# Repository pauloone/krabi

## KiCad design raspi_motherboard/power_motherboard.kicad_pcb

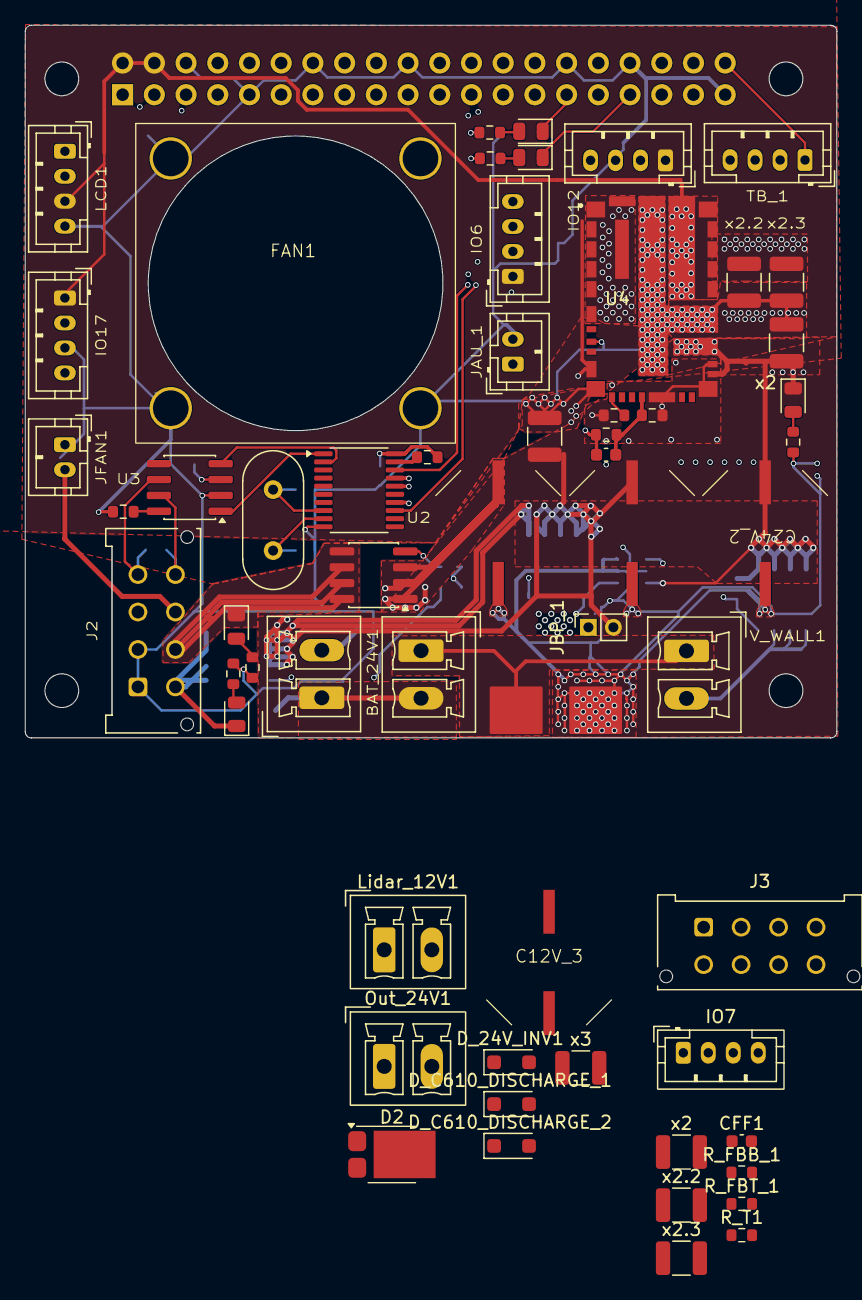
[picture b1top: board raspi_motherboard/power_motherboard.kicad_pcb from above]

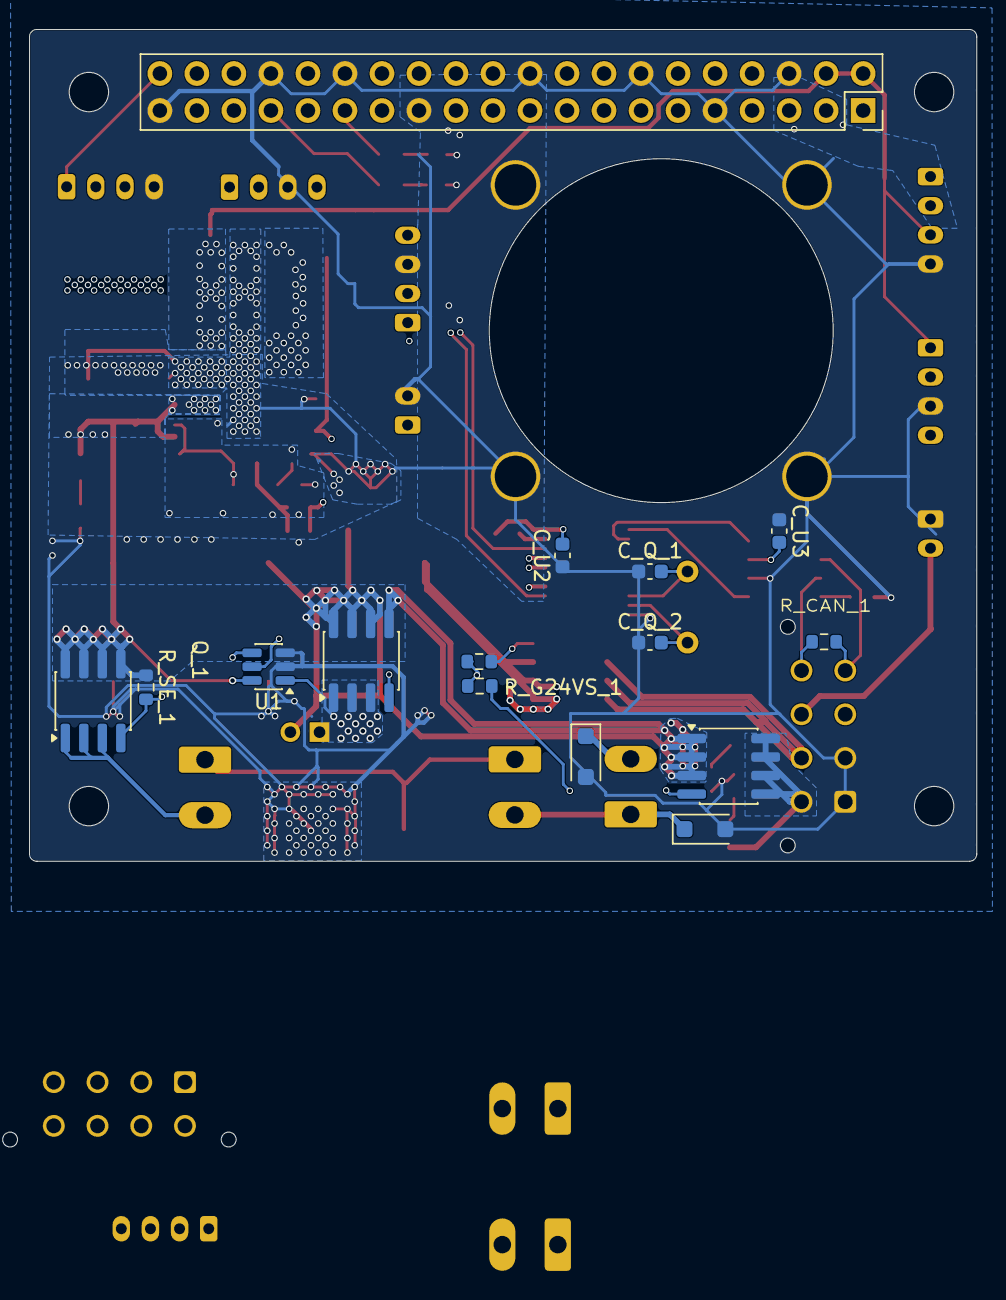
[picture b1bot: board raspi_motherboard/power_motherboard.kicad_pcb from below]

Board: 4 copper layers, 65.0 x 57.1 mm, 78 parts (15 on the bottom side), 48 nets.

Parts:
BAT_12V1, BAT_24V1: Conn_01x02_Pin; PhoenixContact_MCV_1,5_2-G-3.81_1x02_P3.81mm_Vertical
C12V_1, C12V_3, C24V_1, C24V_2: 470µ; CP_Panasonic FN Series G size
C24_V3: 47µ; C_1210_3225Metric
CFF1: C; C_0603_1608Metric
CFF1#2: 58pF; C_0603_1608Metric
C_Q_1, C_Q_2: 22pF; C_0603_1608Metric
C_U2, C_U3: 100nF; C_0603_1608Metric
D2: PMEG045V100EPD; Nexperia_CFP15_SOT-1289
D_12V_INV1, D_24V_INV1, D_24V_INV1#2: D; D_SOD-123F
D_C610_DISCHARGE_1, D_C610_DISCHARGE_2: D; D_SOD-123F
FAN1: Conn_01x02_Socket; FAN_25mm
F_12VE1: Fuse; LittleFuse 154 holder
IO6, IO7, IO12, IO17: Conn_01x04_Socket; JST_PH_B4B-PH-K_1x04_P2.00mm_Vertical
J1: GPIO; PinSocket_2x20_P2.54mm_Vertical
J2, J3: Conn_02x04_Top_Bottom; Molex_Micro-Fit_3.0_43045-0812_2x04_P3.00mm_Vertical
JAU_1: Conn_01x02_Socket; JST_PH_B2B-PH-K_1x02_P2.00mm_Vertical
JBP_1: Conn_01x02_Socket; PinSocket_1x02_P2.00mm_Vertical
JFAN1: Conn_01x02_Socket; JST_PH_B2B-PH-K_1x02_P2.00mm_Vertical
LCD1: Conn_01x04_Socket; JST_PH_B4B-PH-K_1x04_P2.00mm_Vertical
LED_12VS1, LED_24V1, LED_24VS1: LED; LED_0805_2012Metric
LED_R_1, LED_R_2: LED; LED_0805_2012Metric
Lidar_12V1: Conn_01x02_Pin; PhoenixContact_MCV_1,5_2-G-3.81_1x02_P3.81mm_Vertical
MH1, MH2, MH3, MH4: MountingHole_2.7mm_M2.5
Out_24V1: Conn_01x02_Pin; PhoenixContact_MCV_1,5_2-G-3.81_1x02_P3.81mm_Vertical
Q_1, Q_2, Q_12VP_1, Q_24VP_1: RS3L110AT; SOP-8_3.76x4.96mm_P1.27mm
R_CAN_1: 120; R_0603_1608Metric
R_FBB_1, R_FBB_1#2: 10k; R_0603_1608Metric
R_FBT_1, R_FBT_1#2: 41.2k; R_0603_1608Metric
R_G12VS_1, R_G24VS_1: 2.2k; R_0603_1608Metric
R_L12VS1: 2.49k; R_0603_1608Metric
R_L24V1, R_L24VS1: 11k; R_0603_1608Metric
R_LED_R_1, R_LED_R_2: 560; R_0603_1608Metric
R_RESET_1: 10k; R_0603_1608Metric
R_RESET_2: 1k; R_0603_1608Metric
R_SE_1: 470k; R_0603_1608Metric
R_T1, R_T1#2: 25.5k; R_0603_1608Metric
TB_1: Conn_01x04_Socket; JST_PH_B4B-PH-K_1x04_P2.00mm_Vertical
U1: LTC4412xS6; TSOT-23-6
U2: MCP2515-xST; TSSOP-20_4.4x6.5mm_P0.65mm
U3: SN65HVD230; SOIC-8_3.9x4.9mm_P1.27mm
U4: LMZM33606RLXR; IC_LMZM33606RLXR
V_WALL1: Conn_01x02_Pin; PhoenixContact_MCV_1,5_2-G-3.81_1x02_P3.81mm_Vertical
Y1: Crystal; Crystal_HC49-U_Vertical
x2, x2#2, x3: 10µ; C_1210_3225Metric
x2.2, x2.2#2, x2.3, x2.3#2: 47µ; C_1210_3225Metric

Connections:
5V: CFF1.1, CFF1#2.1, IO12.1, J1.2, J1.4, LCD1.3, R_FBT_1.1, R_FBT_1#2.1, U4.10 (BIAS_SEL), U4.24 (VOUT), U4.25 (VOUT), U4.26 (VOUT), U4.27 (VOUT), U4.28 (VOUT), U4.29_36_37 (VOUT), x2.2.1, x2.2#2.1, x2.3.1, x2.3#2.1
12V: BAT_12V1.2, BAT_24V1.1, C12V_1.1, D_12V_INV1.1 (K), D_C610_DISCHARGE_1.1 (K), J2.7, J3.7, JFAN1.2, Lidar_12V1.2, Q_12VP_1.1 (S), Q_12VP_1.2 (S), Q_12VP_1.3 (S)
12V_S: D_C610_DISCHARGE_1.2 (A), J2.6, J3.6, LED_12VS1.1 (K), Q_12VP_1.5 (D), Q_12VP_1.6 (D), Q_12VP_1.7 (D), Q_12VP_1.8 (D)
24V: C24V_1.1, C24V_2.1, C24_V3.1, D2.1 (A), D2.2 (A), D_24V_INV1.1 (K), D_C610_DISCHARGE_2.1 (K), JBP_1.2, LED_24V1.1 (K), Out_24V1.2, Q_1.5 (D), Q_1.6 (D), Q_1.7 (D), Q_1.8 (D), Q_2.5 (D), Q_2.6 (D), Q_2.7 (D), Q_2.8 (D), Q_24VP_1.1 (S), Q_24VP_1.2 (S), Q_24VP_1.3 (S), R_SE_1.1, U1.6 (SENSE), U4.20 (EN), U4.22_39 (VIN), x2#2.1
24V_BAT: D_24V_INV1#2.1 (K), JBP_1.1, Q_1.1 (S), Q_1.2 (S), Q_1.3 (S), U1.1 (VIN)
24V_S: D_C610_DISCHARGE_2.2 (A), J2.5, J3.5, LED_24VS1.1 (K), Q_24VP_1.5 (D), Q_24VP_1.6 (D), Q_24VP_1.7 (D), Q_24VP_1.8 (D)
+3V3: C_U2.2, C_U3.2, J1.1, J1.17, R_RESET_1.2, U2.20 (VDD), U3.3 (VCC)
/GPIO5: J1.29, LED_R_2.1 (K)
/GPIO13/PWM1: J1.33, LED_R_1.1 (K)
/power/5V_raspi/24V: C12V_3.1, D2.3 (K), x2.1, x3.1
AGND: R_FBB_1.2, R_FBB_1#2.2, R_T1.1, R_T1#2.1, U4.16 (AGND), U4.19 (SYNC/MODE), U4.21 (AGND)
AU: JAU_1.1, R_G12VS_1.2, R_G24VS_1.2
CAN_H: J2.8, J3.8, R_CAN_1.1, U3.7 (CANH)
CAN_L: J2.4, J3.4, R_CAN_1.2, U3.6 (CANL)
GND: C12V_1.2, C12V_3.2, C24V_1.2, C24V_2.2, C24_V3.2, C_Q_1.1, C_Q_2.1, C_U2.1, C_U3.1, D_12V_INV1.2 (A), D_24V_INV1.2 (A), D_24V_INV1#2.2 (A), FAN1.1, F_12VE1.2, IO6.2, IO7.2, IO12.3, IO17.2, J1.6, J1.9, J1.14, J1.20, J1.25, J1.30, J1.34, J1.39, J2.1, J2.2, J2.3, J3.1, J3.2, J3.3, JAU_1.2, JFAN1.1, LCD1.4, R_L12VS1.1, R_L24V1.1, R_L24VS1.1, R_LED_R_1.1, R_LED_R_2.1, R_RESET_2.1, TB_1.4, U1.2 (GND), U1.3 (CTL), U2.10 (VSS), U3.2 (GND), U4.8 (PGND), U4.11 (PGND), U4.23_38_40_41 (PGND), U4.30_34_35 (PGND), x2.2, x2#2.2, x2.2.2, x2.2#2.2, x2.3.2, x2.3#2.2, x3.2
unnamed: BAT_12V1.1, F_12VE1.1
unnamed: LED_12VS1.2 (A), R_L12VS1.2
unnamed: LED_24V1.2 (A), R_L24V1.2
unnamed: LED_24VS1.2 (A), R_L24VS1.2
unnamed: LED_R_1.2 (A), R_LED_R_1.2
unnamed: LED_R_2.2 (A), R_LED_R_2.2
unnamed: Q_1.4 (G), U1.5 (GATE)
unnamed: Q_2.4 (G), R_SE_1.2, U1.4 (STAT)
unnamed: Q_12VP_1.4 (G), R_G12VS_1.1
unnamed: Q_24VP_1.4 (G), R_G24VS_1.1
unnamed: C_Q_2.2, U2.9 (OSC1), Y1.2
unnamed: C_Q_1.2, U2.8 (OSC2), Y1.1
unnamed: U2.2 (RXCAN), U3.4 (R)
unnamed: U2.1 (TXCAN), U3.1 (D)
unnamed: R_RESET_1.1, U2.19 (~RESET)
unnamed: R_RESET_2.2, U3.8 (Rs)
unnamed: CFF1.2, CFF1#2.2, R_FBB_1.1, R_FBB_1#2.1, R_FBT_1.2, R_FBT_1#2.2, U4.15 (FB)
unnamed: R_T1.2, R_T1#2.2, U4.12 (RT)
R_CEO: J1.24, U2.18 (~CS)
R_CLK: J1.23, U2.14 (SCK)
R_IO6: IO6.1, J1.31
R_IO12: IO7.1, IO12.2, J1.32
R_IO16: J1.36, TB_1.3
R_IO17: IO17.1, J1.11
R_IO20: J1.38, TB_1.2
R_IO21: J1.40, TB_1.1
R_IO25: J1.22, U2.13 (~INT)
R_MISO: J1.21, U2.17 (SO)
R_MOSI: J1.19, U2.16 (SI)
SCL: J1.5, LCD1.1
SDA: J1.3, LCD1.2
SW: U4.1 (SW), U4.2 (SW), U4.3 (SW), U4.4 (SW), U4.5 (SW), U4.6 (SW), U4.31 (SW), U4.32_33 (SW)
WALL_20V: Q_2.1 (S), Q_2.2 (S), Q_2.3 (S), V_WALL1.2

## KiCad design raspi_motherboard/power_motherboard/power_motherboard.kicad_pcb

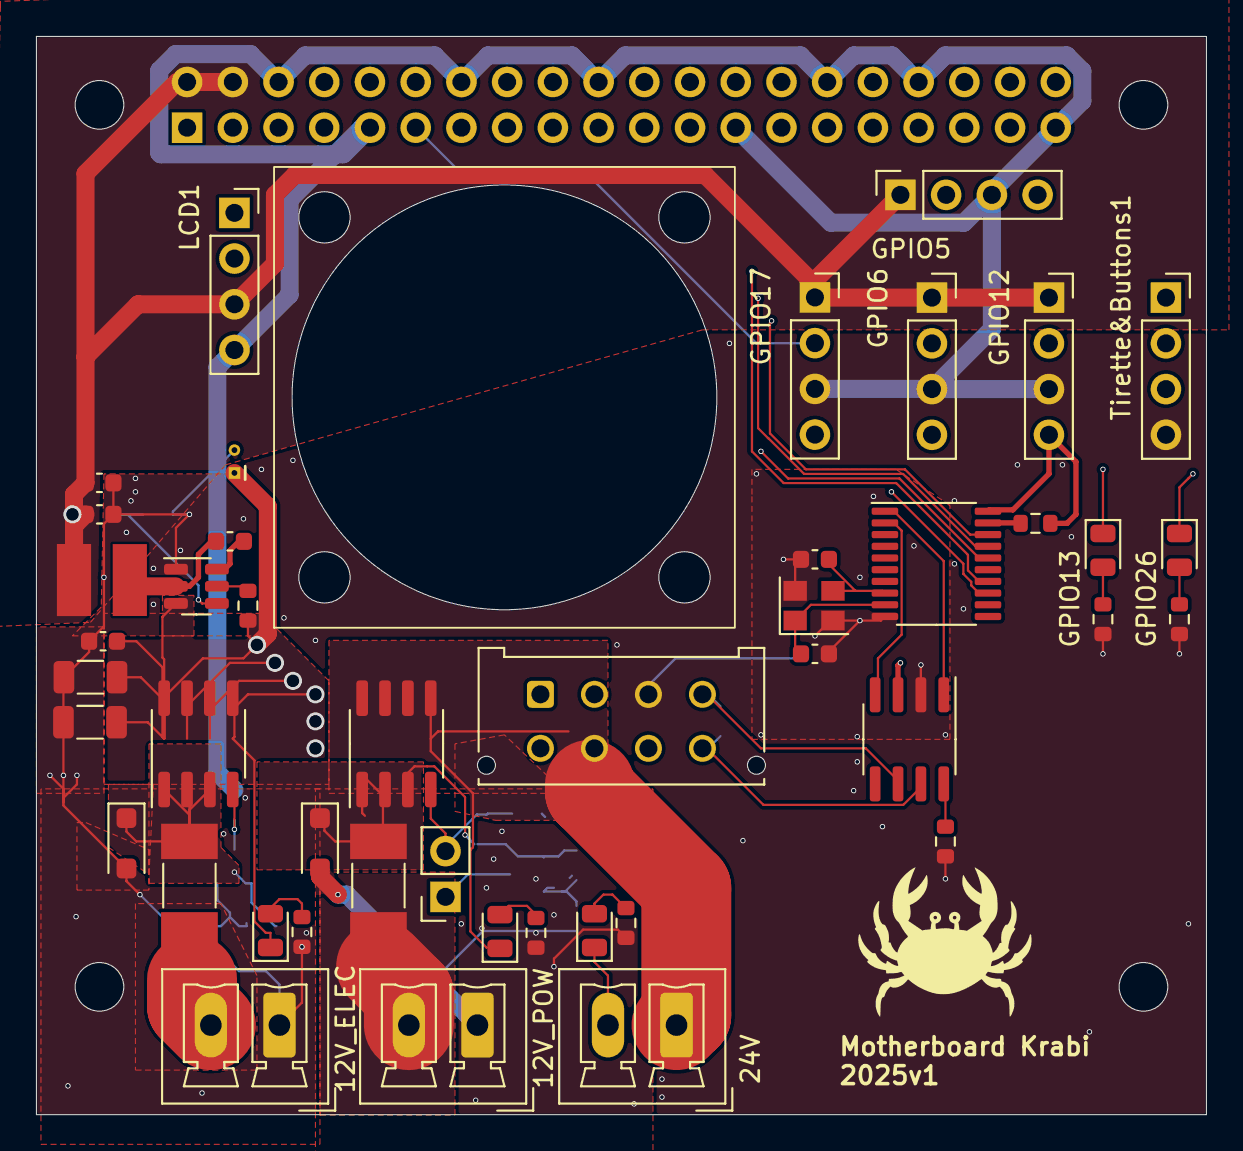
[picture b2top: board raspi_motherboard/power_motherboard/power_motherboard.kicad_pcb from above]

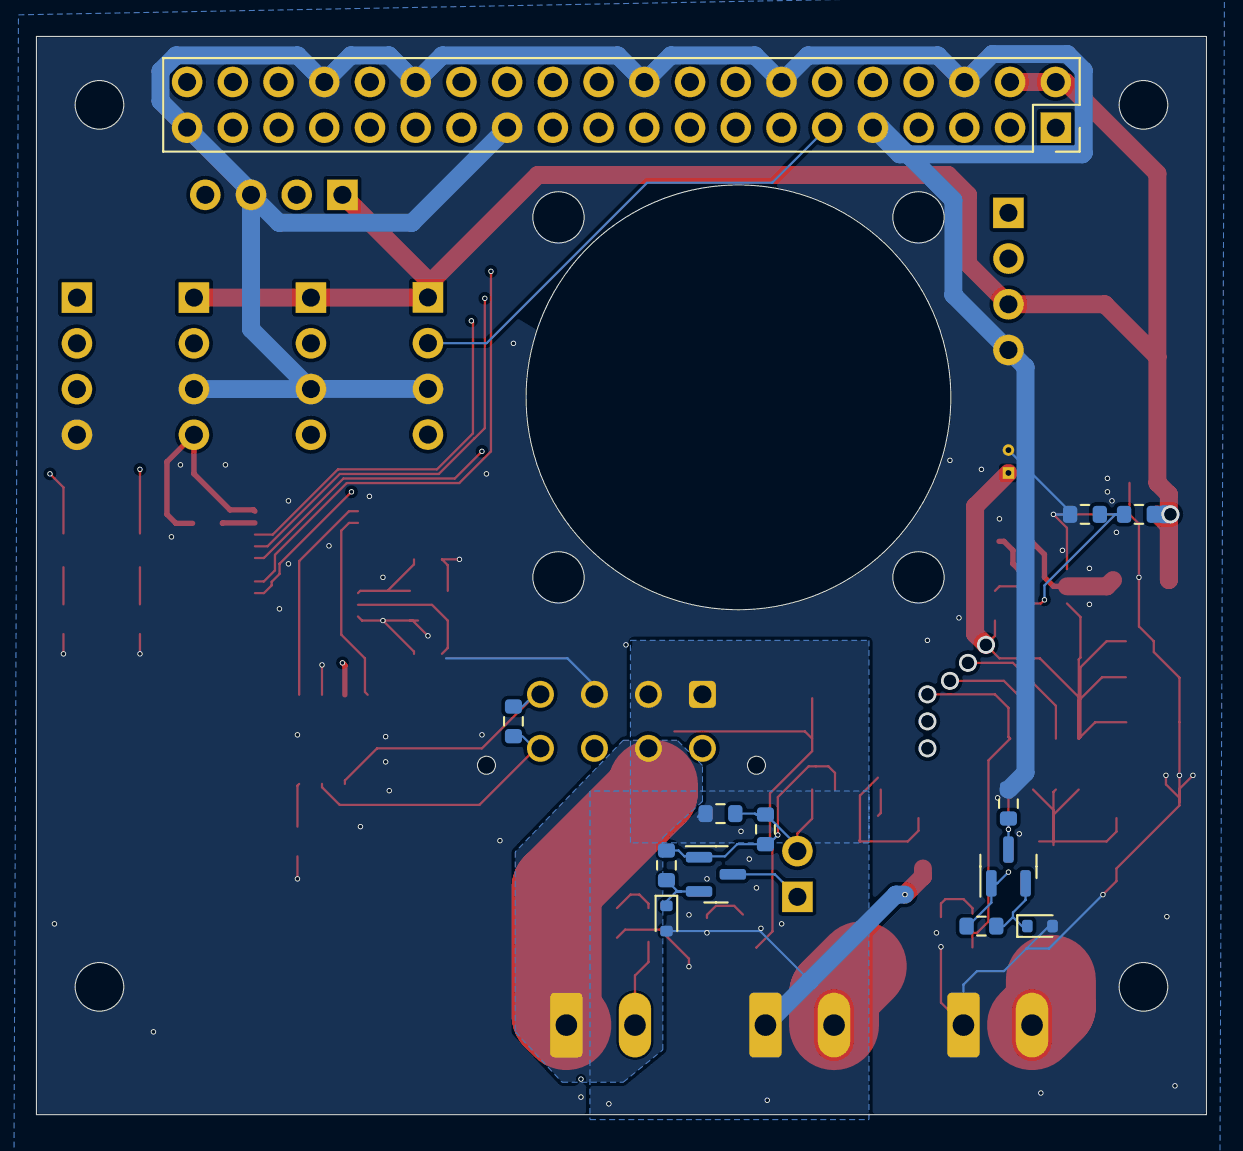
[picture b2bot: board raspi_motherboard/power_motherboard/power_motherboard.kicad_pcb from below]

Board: 4 copper layers, 65.0 x 59.9 mm, 61 parts (13 on the bottom side), 49 nets.

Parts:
BAT_12V_P1, BAT_24V1: Conn_01x02_Pin; PhoenixContact_MCV_1,5_2-G-3.81_1x02_P3.81mm_Vertical
BAT_ELEC1: Conn_01x02_Pin; PhoenixContact_MCV_1,5_2-G-3.81_1x02_P3.81mm_Vertical
C1, C2: 22pF; C_0603_1608Metric
C_BST_1: 0.1µ; C_0603_1608Metric
C_IN_1, C_IN_2: 10µ; C_1206_3216Metric
C_IN_3: 0.1µ; C_0603_1608Metric
C_OUT_1, C_OUT_2: 22µ; C_0603_1608Metric
D_12VE_INV1: D; D_SOD-123F
D_12VE_OT1, D_12VP_OT1: EDZV13B; D_SOD-523
D_12VP_INV1: D_SOD-123F
FAN1: Conn_01x02_Socket; FAN_25mm
F_12VE1, F_12VP1: Fuse; Fuse_Littelfuse-NANO2-451_453
GPIO5, GPIO6, GPIO12, GPIO17: Conn_01x04_Socket; PinSocket_1x04_P2.54mm_Vertical
J1: GPIO; PinSocket_2x20_P2.54mm_Vertical
J2: Conn_02x04_Top_Bottom; Molex_Micro-Fit_3.0_43045-0812_2x04_P3.00mm_Vertical
J3: Conn_01x03; PinSocket_1x02_P2.54mm_Vertical
L2: 3.3µH; VLS4020CX-H
LCD1: Conn_01x04_Socket; PinSocket_1x04_P2.54mm_Vertical
LED_12V_ELEC_1, LED_12V_POW_1, LED_24V_POW_1: LED; LED_0805_2012Metric
LED_R_1, LED_R_2: LED; LED_0805_2012Metric
MH1, MH2, MH3, MH4: MountingHole_2.7mm_M2.5
Q_12VP_1, Q_12VP_2: RS3L110AT; SOP-8_3.76x4.96mm_P1.27mm
Q_P12VE_1, Q_P12VP_1: 2N3906; SOT-23
R_12VE_1, R_12VP_1: 10k; R_0603_1608Metric
R_12VE_2, R_12VP_2: 2.2k; R_0603_1608Metric
R_12VP_3: 1M; R_0603_1608Metric
R_CAN1: 120; R_0603_1608Metric
R_EN_1: 10k; R_0603_1608Metric
R_FB_1: 10k; R_0603_1608Metric
R_FB_2: 54.9k; R_0603_1608Metric
R_LED_12V_ELEC_1, R_LED_12V_POW_1: 2.49k; R_0603_1608Metric
R_LED_24V_POW_1: 11k; R_0603_1608Metric
R_LED_R_1, R_LED_R_2: 560; R_0603_1608Metric
R_RESET1: 10k; R_0603_1608Metric
R_RESET2: 1k; R_0603_1608Metric
Tirette&Buttons1: Conn_01x04_Socket; PinSocket_1x04_P2.54mm_Vertical
U1: MCP2515-xST; TSSOP-20_4.4x6.5mm_P0.65mm
U2: SN65HVD230; SOIC-8_3.9x4.9mm_P1.27mm
U3: TPS563200; SOT-23-6
Y1: AMB8-12Mhz; Oscillator_SMD_Abracon_ASE-4Pin_3.2x2.5mm

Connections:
3_3V: GPIO5.4, GPIO6.4, GPIO12.4, GPIO17.4, J1.1, J1.17, R_RESET1.2, U1.20 (VDD), U2.3 (VCC)
5V: C_OUT_1.1, C_OUT_2.1, GPIO5.1, GPIO6.1, GPIO12.1, GPIO17.1, J1.2, J1.4, L2.2, LCD1.3, R_FB_2.2
12VP_SEC_1: J3.2, Q_12VP_2.4 (G), R_12VP_2.1, R_12VP_3.2
12VP_SEC_2: J3.1, Q_P12VP_1.3 (C)
12V_ELEC: BAT_ELEC1.2, F_12VE1.2
12V_ELEC_P: C_IN_1.1, C_IN_2.1, C_IN_3.1, FAN1.1, J2.7, LED_12V_ELEC_1.1 (K), Q_12VP_1.5 (D), Q_12VP_1.6 (D), Q_12VP_1.7 (D), Q_12VP_1.8 (D), R_EN_1.1, U3.3 (VIN)
12V_POWER: BAT_12V_P1.2, F_12VP1.2
12V_POW_P: BAT_24V1.1, J2.6, LED_12V_POW_1.1 (K), Q_12VP_2.5 (D), Q_12VP_2.6 (D), Q_12VP_2.7 (D), Q_12VP_2.8 (D)
24V_POW_P: BAT_24V1.2, J2.5, LED_24V_POW_1.1 (K)
/GPIO13/PWM1: J1.33, LED_R_1.1 (K)
/GPIO26: J1.37, LED_R_2.1 (K)
CAN_H: J2.8, R_CAN1.2, U2.7 (CANH)
CAN_L: J2.4, R_CAN1.1, U2.6 (CANL)
GND_ELEC: BAT_ELEC1.1, C1.1, C2.1, C_IN_1.2, C_IN_2.2, C_IN_3.2, C_OUT_1.2, C_OUT_2.2, D_12VE_INV1.2 (A), D_12VE_OT1.2 (A), FAN1.2, GPIO5.3, GPIO6.3, GPIO12.3, GPIO17.3, J1.6, J1.9, J1.14, J1.20, J1.25, J1.30, J1.34, J1.39, J2.3, LCD1.4, R_12VE_2.2, R_FB_1.2, R_LED_12V_ELEC_1.1, R_LED_R_1.1, R_LED_R_2.1, R_RESET2.1, Tirette&Buttons1.4, U1.10 (VSS), U2.2 (GND), U3.1 (GND), Y1.2, Y1.4
GND_POW: BAT_12V_P1.1, D_12VP_INV1.2 (A), D_12VP_OT1.2 (A), J2.1, J2.2, R_12VP_2.2, R_LED_12V_POW_1.1, R_LED_24V_POW_1.1
unnamed: D_12VE_INV1.1 (K), F_12VE1.1, Q_12VP_1.1 (S), Q_12VP_1.2 (S), Q_12VP_1.3 (S), Q_P12VE_1.1 (E), R_12VE_1.1
unnamed: D_12VE_OT1.1 (K), Q_P12VE_1.2 (B), R_12VE_1.2
unnamed: D_12VP_INV1.1 (K), F_12VP1.1, Q_12VP_2.1 (S), Q_12VP_2.2 (S), Q_12VP_2.3 (S), Q_P12VP_1.1 (E), R_12VP_1.1, R_12VP_3.1
unnamed: D_12VP_OT1.1 (K), Q_P12VP_1.2 (B), R_12VP_1.2
unnamed: LED_12V_ELEC_1.2 (A), R_LED_12V_ELEC_1.2
unnamed: LED_12V_POW_1.2 (A), R_LED_12V_POW_1.2
unnamed: LED_24V_POW_1.2 (A), R_LED_24V_POW_1.2
unnamed: LED_R_1.2 (A), R_LED_R_1.2
unnamed: LED_R_2.2 (A), R_LED_R_2.2
unnamed: Q_12VP_1.4 (G), Q_P12VE_1.3 (C), R_12VE_2.1
unnamed: C1.2, U1.9 (OSC1), Y1.1
unnamed: C2.2, U1.8 (OSC2), Y1.3
unnamed: U1.2 (RXCAN), U2.4 (R)
unnamed: U1.1 (TXCAN), U2.1 (D)
unnamed: R_RESET1.1, U1.19 (~RESET)
unnamed: R_RESET2.2, U2.8 (Rs)
unnamed: R_EN_1.2, U3.5 (EN)
unnamed: C_BST_1.1, L2.1, U3.2 (SW)
unnamed: C_BST_1.2, U3.6 (VBST)
unnamed: R_FB_1.1, R_FB_2.1, U3.4 (VFB)
R_CEO: J1.24, U1.18 (~CS)
R_CLK: J1.23, U1.14 (SCK)
R_IO5: GPIO5.2, J1.29
R_IO6: GPIO6.2, J1.31
R_IO12: GPIO12.2, J1.32
R_IO16: J1.36, Tirette&Buttons1.3
R_IO17: GPIO17.2, J1.11
R_IO20: J1.38, Tirette&Buttons1.2
R_IO21: J1.40, Tirette&Buttons1.1
R_IO25: J1.22, U1.13 (~INT)
R_MISO: J1.21, U1.17 (SO)
R_MOSI: J1.19, U1.16 (SI)
SDA: J1.3, LCD1.2
SDL: J1.5, LCD1.1

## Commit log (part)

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2025-01-19 Initial commit: working motherboard
2025-01-19 Add logo
2025-01-21 small fixes
2025-01-21 add Tirette&Buttons connector (not routed yet, as the CAN schematic is broken)
2025-01-22 Update the start button & kicad 8
2025-01-23 fix ERC/DRC (including short-circuits) + add flood fills
2025-01-23 Commit missed element
2025-01-23 fix a few flood-fills and antennas
2025-01-23 Fix double line + priority
2025-01-28 fix antennas (mainly on internal copper) + add labels
2025-01-28 [WiP] start putting refs in silkscreen
2025-10-26 Last update
2025-11-08 V2 of the board: 24 Volt power
2025-11-09 Routed
2025-11-11 Changing connectors
2026-01-15 Production version
